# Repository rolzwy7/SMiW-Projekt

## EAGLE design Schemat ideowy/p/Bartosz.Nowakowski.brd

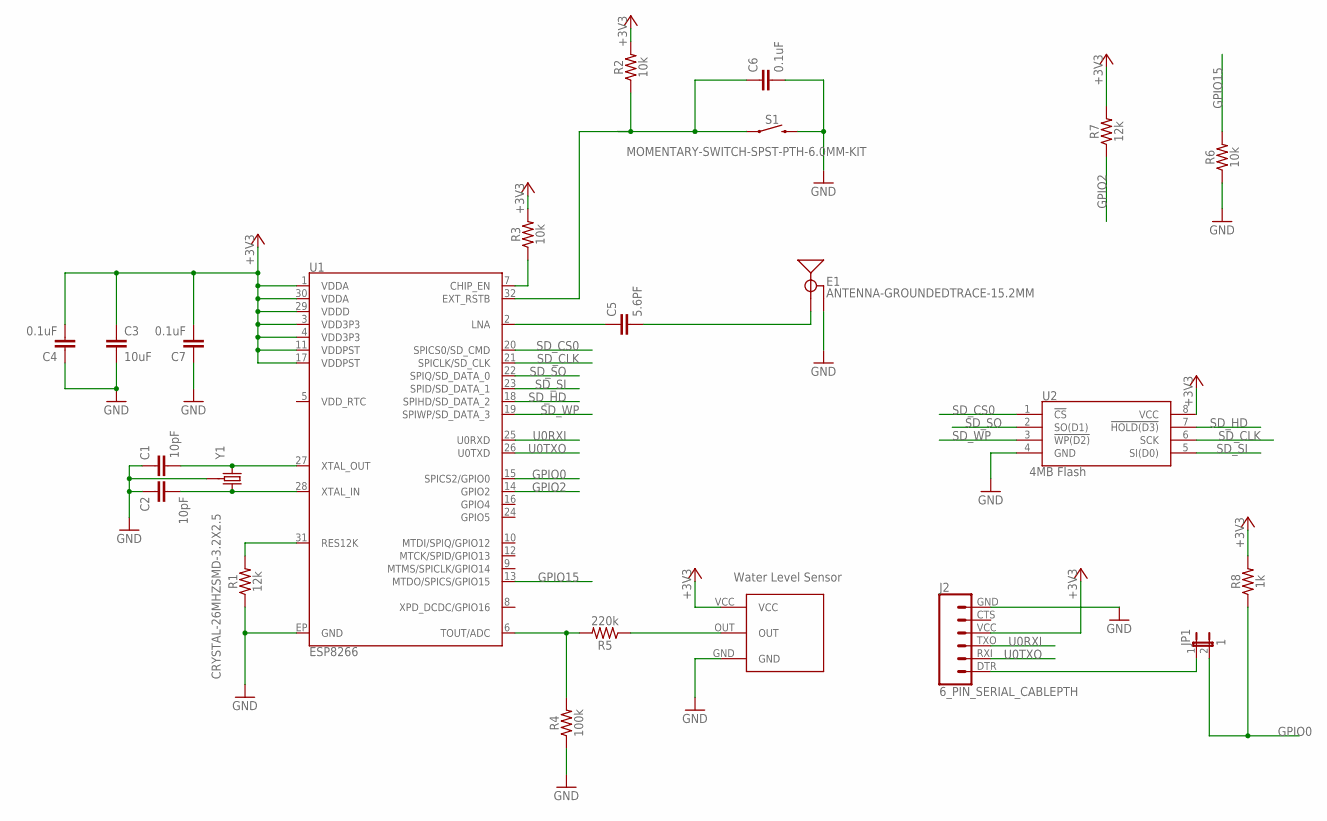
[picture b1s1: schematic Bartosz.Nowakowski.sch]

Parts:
C1, C2: 10pF; 0603
C3: 10uF; 0805
C4, C6, C7: 0.1uF; 0603
C5: 5.6PF; 0603
E1: ANTENNA-GROUNDEDTRACE-15.2MM; TRACE_ANTENNA_2.4GHZ_15.2MM
J2: 6_PIN_SERIAL_CABLEPTH; FTDI_BASIC
JP1: 1; JP1
R1, R7: 12k; 0603
R2, R3, R6: 10k; 0603
R4: 100k; 0603
R5: 220k; 0603
R8: 1k; 0603
S1: MOMENTARY-SWITCH-SPST-PTH-6.0MM-KIT; TACTILE_SWITCH_PTH_6.0MM_KIT
U1: ESP8266; QFN32-5X5MM
U2: 4MB Flash; SO08
WATER1: WATERLEVELSENORDEV; WATERLEVELSENSORFT
Y1: CRYSTAL-26MHZSMD-3.2X2.5; CRYSTAL-SMD-3.2X2.5MM

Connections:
+3V3: C3.1, C4.2, C7.2, J2.VCC (4), R2.2, R3.2, R7.2, R8.2, U1.1 (VDDA), U1.3 (VDD3P3), U1.4 (VDD3P3), U1.11 (VDDPST), U1.17 (VDDPST), U1.29 (VDDD), U1.30 (VDDA), U2.8 (VCC), WATER1.VCC
GND: C1.1, C2.1, C3.2, C4.1, C6.2, C7.1, E1.GND, J2.GND (6), R1.1, R4.1, R6.1, S1.3 (2), U1.EP (GND), U2.4 (GND), WATER1.GND, Y1.2 (3), Y1.4 (3)
GPIO0: JP1.2, R8.1, U1.15 (SPICS2/GPIO0)
GPIO2: R7.1, U1.14 (GPIO2)
GPIO15: R6.2, U1.13 (MTDO/SPICS/GPIO15)
unnamed: R1.2, U1.31 (RES12K)
unnamed: C1.2, U1.27 (XTAL_OUT), Y1.1
unnamed: C2.2, U1.28 (XTAL_IN), Y1.3 (2)
unnamed: R3.1, U1.7 (CHIP_EN)
unnamed: C6.1, R2.1, S1.1, U1.32 (EXT_RSTB)
unnamed: C5.1, U1.2 (LNA)
unnamed: C5.2, E1.ANT (SIGNAL)
unnamed: R4.2, R5.2, U1.6 (TOUT/ADC)
unnamed: R5.1, WATER1.OUT
unnamed: J2.DTR (1), JP1.1
SD_CLK: U1.21 (SPICLK/SD_CLK), U2.6 (SCK)
SD_CS0: U1.20 (SPICS0/SD_CMD), U2.1 (!CS)
SD_HD: U1.18 (SPIHD/SD_DATA_2), U2.7 (!HOLD(D3))
SD_SI: U1.23 (SPID/SD_DATA_1), U2.5 (SI(D0))
SD_SO: U1.22 (SPIQ/SD_DATA_0), U2.2 (SO(D1))
SD_WP: U1.19 (SPIWP/SD_DATA_3), U2.3 (!WP(D2))
U0RXI: J2.TXO (3), U1.25 (U0RXD)
U0TXO: J2.RXI (2), U1.26 (U0TXD)

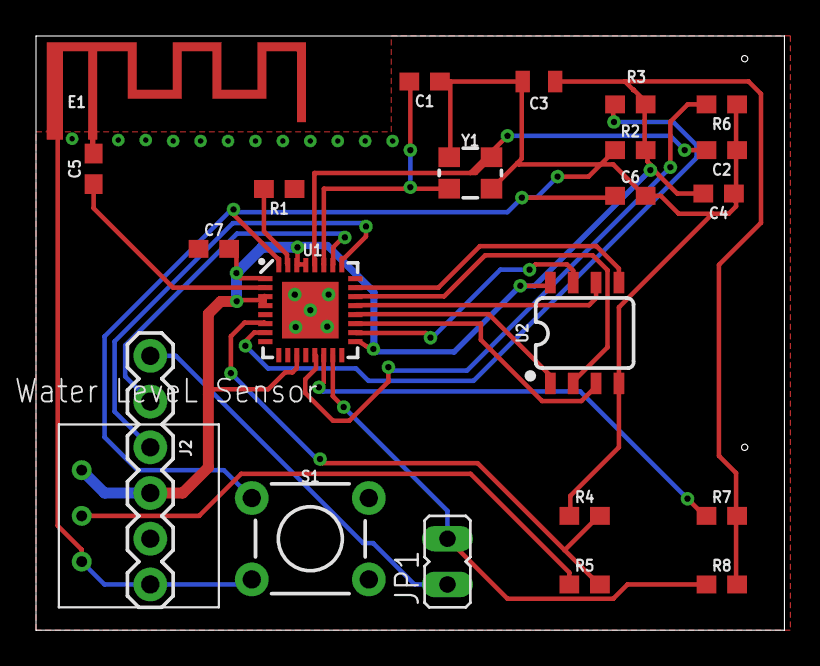
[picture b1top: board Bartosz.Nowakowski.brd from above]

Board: 2 copper layers, 41.6 x 33.0 mm, 23 parts (0 on the bottom side), 23 nets.

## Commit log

2020-08-27 Update program.ino
    Cg

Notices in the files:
parts and their libraries:
SparkFun-RF: Licensing: Creative Commons ShareAlike 4.0 International - https://creativecommons.org/licenses/by-sa/4.0
